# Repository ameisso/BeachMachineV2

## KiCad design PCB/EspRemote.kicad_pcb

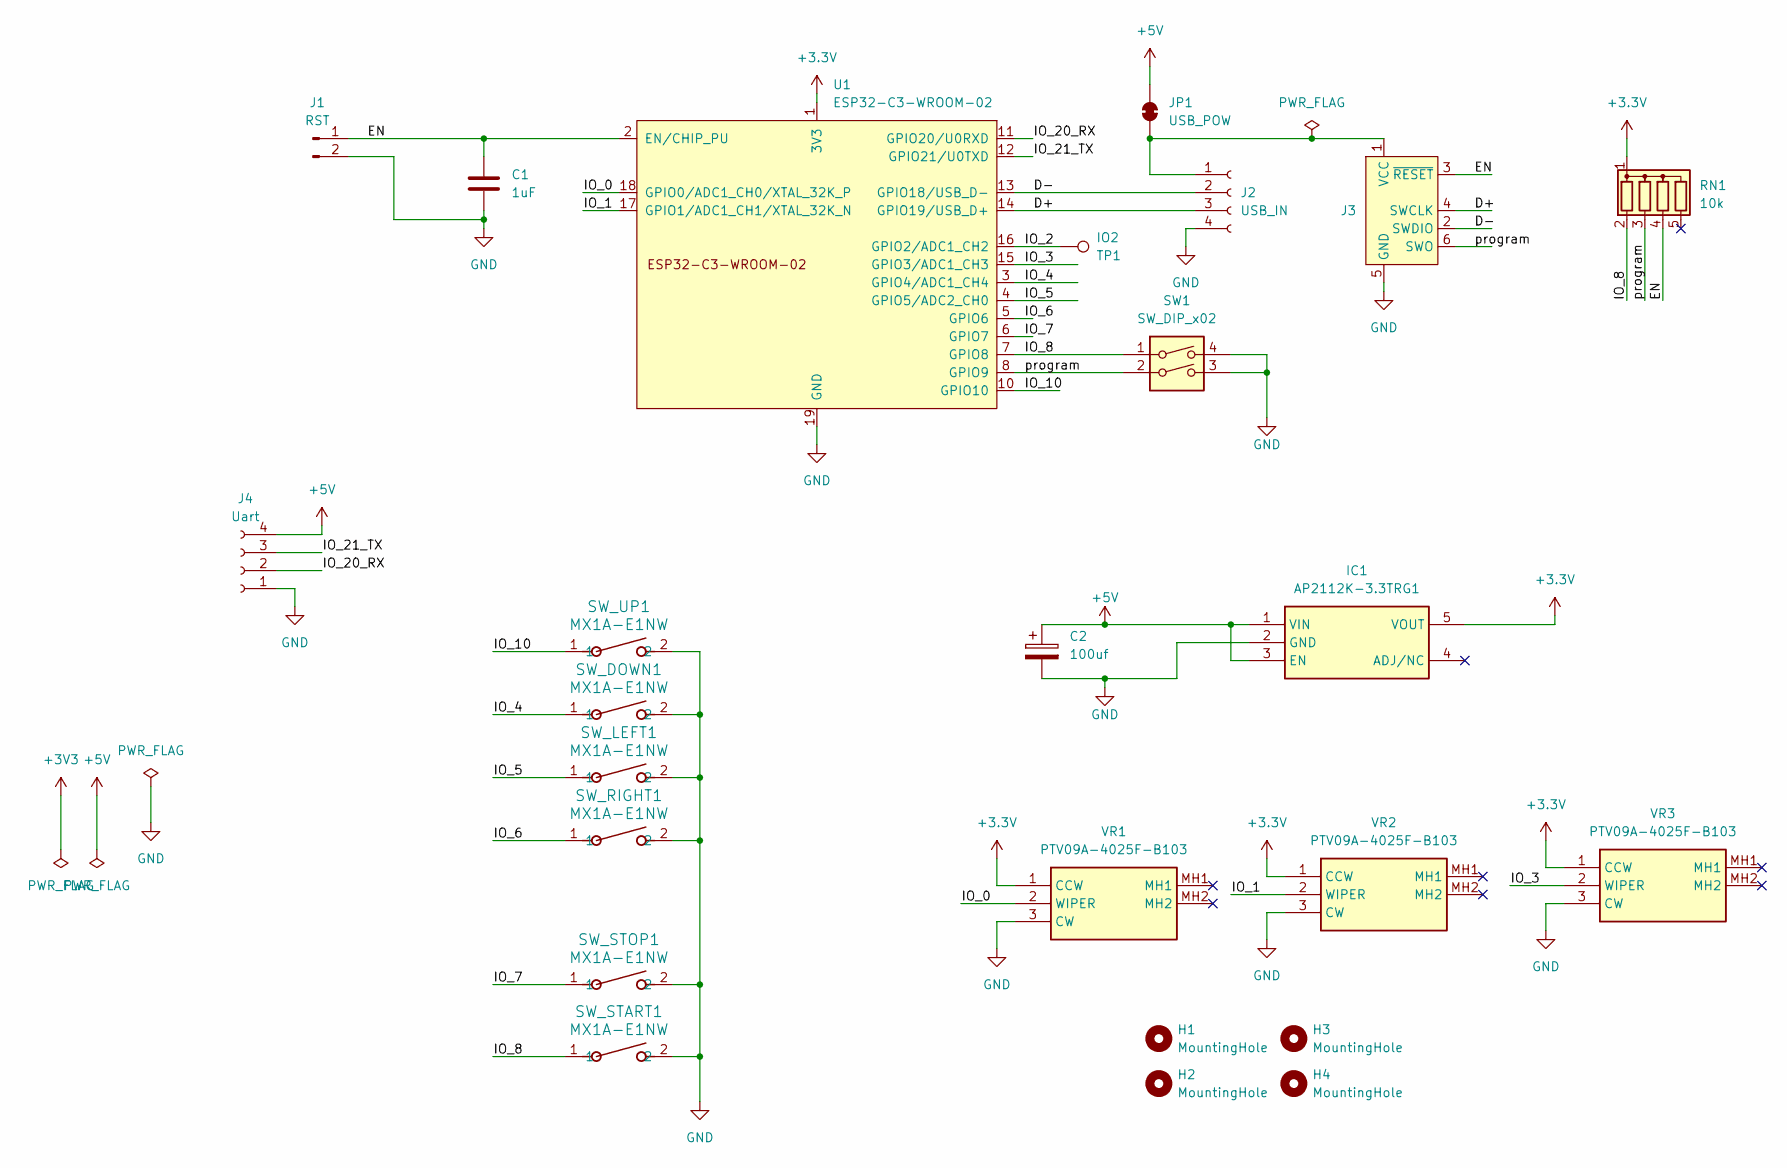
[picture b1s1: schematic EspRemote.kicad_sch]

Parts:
C1: 1uF; C_Rect_L7.2mm_W2.5mm_P5.00mm_FKS2_FKP2_MKS2_MKP2
C2: 100uf; CP_Radial_D8.0mm_P3.50mm
H1, H2, H3, H4: MountingHole; MountingHole_3.2mm_M3
IC1: AP2112K-3.3TRG1; SOT-23-5_handsoldering; Manufacturer_Part_Number AP2112K-3.3TRG1; Mouser Part Number 621-AP2112K-3.3TRG1
J1: RST; PinHeader_1x02_P2.54mm_Vertical
J2: USB_IN; PinHeader_1x04_P2.54mm_Vertical
J3: Conn_ARM_SWD_TagConnect_TC2030-NL; Tag-Connect_TC2030-IDC-NL_2x03_P1.27mm_Vertical
J4: Uart; KF301-4P screw terminal P5mm
JP1: USB_POW; SolderJumper-2_P1.3mm_Bridged_Pad1.0x1.5mm
RN1: 10k; R_Array_SIP5
SW1: SW_DIP_x02; SW_DIP_SPSTx02_Slide_9.78x7.26mm_W7.62mm_P2.54mm
SW_DOWN1: MX1A-E1NW; SW_Cherry_MX_1.00u_PCB
SW_LEFT1: MX1A-E1NW; SW_Cherry_MX_1.00u_PCB
SW_RIGHT1: MX1A-E1NW; SW_Cherry_MX_1.00u_PCB
SW_START1: MX1A-E1NW; SW_Cherry_MX_1.00u_PCB
SW_STOP1: MX1A-E1NW; SW_Cherry_MX_1.00u_PCB
SW_UP1: MX1A-E1NW; SW_Cherry_MX_1.00u_PCB
TP1: IO2; TestPoint_THTPad_1.0x1.0mm_Drill0.5mm
U1: ESP32-C3-WROOM-02
VR1, VR2, VR3: PTV09A-4025F-B103; PTV09A4015FB103; Manufacturer_Part_Number PTV09A-4025F-B103; Mouser Part Number 652-PTV09A-4025FB103

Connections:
+3.3V: IC1.5 (VOUT), RN1.1 (common), U1.1 (3V3), VR1.1 (CCW), VR2.1 (CCW), VR3.1 (CCW)
+5V: C2.1, IC1.1 (VIN), IC1.3 (EN), J4.4, JP1.2 (B)
/D+: J2.3, J3.4 (SWCLK), U1.14 (GPIO19/USB_D+)
/D-: J2.2, J3.2 (SWDIO), U1.13 (GPIO18/USB_D-)
/EN: C1.1, J1.1, J3.3 (~RESET), RN1.4 (R3), U1.2 (EN/CHIP_PU)
/IO_0: U1.18 (GPIO0/ADC1_CH0/XTAL_32K_P), VR1.2 (WIPER)
/IO_1: U1.17 (GPIO1/ADC1_CH1/XTAL_32K_N), VR2.2 (WIPER)
/IO_2: TP1.1, U1.16 (GPIO2/ADC1_CH2)
/IO_3: U1.15 (GPIO3/ADC1_CH3), VR3.2 (WIPER)
/IO_4: SW_DOWN1.1, U1.3 (GPIO4/ADC1_CH4)
/IO_5: SW_LEFT1.1, U1.4 (GPIO5/ADC2_CH0)
/IO_6: SW_RIGHT1.1, U1.5 (GPIO6)
/IO_7: SW_STOP1.1, U1.6 (GPIO7)
/IO_8: RN1.2 (R1), SW1.1, SW_START1.1, U1.7 (GPIO8)
/IO_10: SW_UP1.1, U1.10 (GPIO10)
/IO_20_RX: J4.2, U1.11 (GPIO20/U0RXD)
/IO_21_TX: J4.3, U1.12 (GPIO21/U0TXD)
/program: J3.6 (SWO), RN1.3 (R2), SW1.2, U1.8 (GPIO9)
GND: C1.2, C2.2, IC1.2 (GND), J1.2, J2.4, J3.5 (GND), J4.1, SW1.3, SW1.4, SW_DOWN1.2, SW_LEFT1.2, SW_RIGHT1.2, SW_START1.2, SW_STOP1.2, SW_UP1.2, U1.9 (GND), U1.19 (GND), VR1.3 (CW), VR2.3 (CW), VR3.3 (CW)
unnamed: J2.1, J3.1 (VCC), JP1.1 (A)

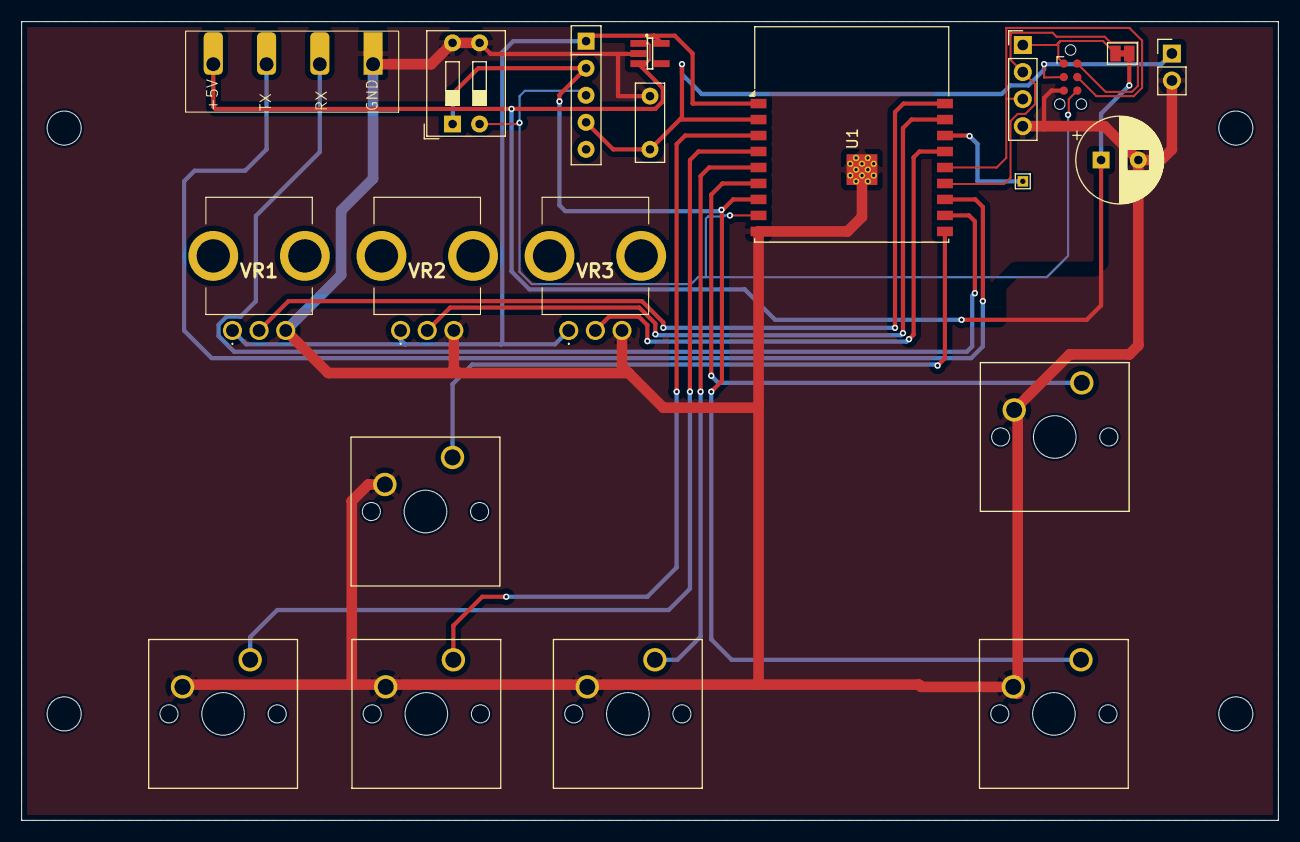
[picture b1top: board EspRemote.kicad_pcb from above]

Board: 2 copper layers, 118.0 x 75.0 mm, 25 parts (0 on the bottom side), 20 nets.

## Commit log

2025-01-19 New : first pcb batch
2025-01-19 New : first compiling code
2025-01-19 New : config Files
2025-01-22 New : telnet option
2025-01-22 New : program loop
2025-01-22 New : prog name
2025-02-08 New : wiring manual
2025-02-08 New : Servo + Dual Y out
2025-02-08 Fix : soft limit and servo range
2025-02-10 New : config file v2
2025-02-10 Fix : steps/mm
2025-02-10 New : release alarms
2025-02-11 Fix : startup offset for servo
2025-02-11 New : restart controller at zero (to ensure Z machine position at 0)
2025-02-11 New : button handler structure
2025-02-16 New : first pcb buildup code
2025-02-16 Fix : reconnect wifi on play
2025-02-16 New : play manapelle
2025-02-16 Clean : dead logs
2025-02-16 Refactor : telnet prints
2025-02-16 New : restart wifi on jog
2025-02-16 Refactor : prints
2025-02-26 New : V3 file
2025-02-26 New : startup square
2025-02-26 New : offsetedFile
2025-02-26 New : offsets
2025-02-26 Fix : Nan
2025-02-26 New : shipped files for Amiens
